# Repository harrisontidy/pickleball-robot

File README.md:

# Autonomous Pickleball Robot

An autonomous robot being developed to play pickleball against a human. It is designed to watch an incoming shot, move into position, and swing a paddle to return the ball across the net.

The goal is to create a practice partner that can react to your shots and keep a rally going.

## Playing a rally

The planned vision system uses a camera and YOLO object detection to locate the pickleball and follow its movement. From successive observations, the robot estimates where the ball is heading and where it needs to meet it.

The mobile base moves into position while the arm adjusts the paddle's angle. The swing mechanism is designed to time the stroke with the ball's arrival, return the shot, and bring the paddle back into position for the next ball.

The intended rally follows a continuous cycle:

1. Detect the incoming ball.
2. Track its path and estimate an interception point.
3. Move into position and line up the paddle.
4. Swing to return the shot.
5. Reset and watch for the next ball.

## Manual control

The robot also has a phone control page for driving, adjusting the paddle joints, and triggering swing sequences. These controls let the drive and paddle movements be tested individually while the autonomous rally system is developed.

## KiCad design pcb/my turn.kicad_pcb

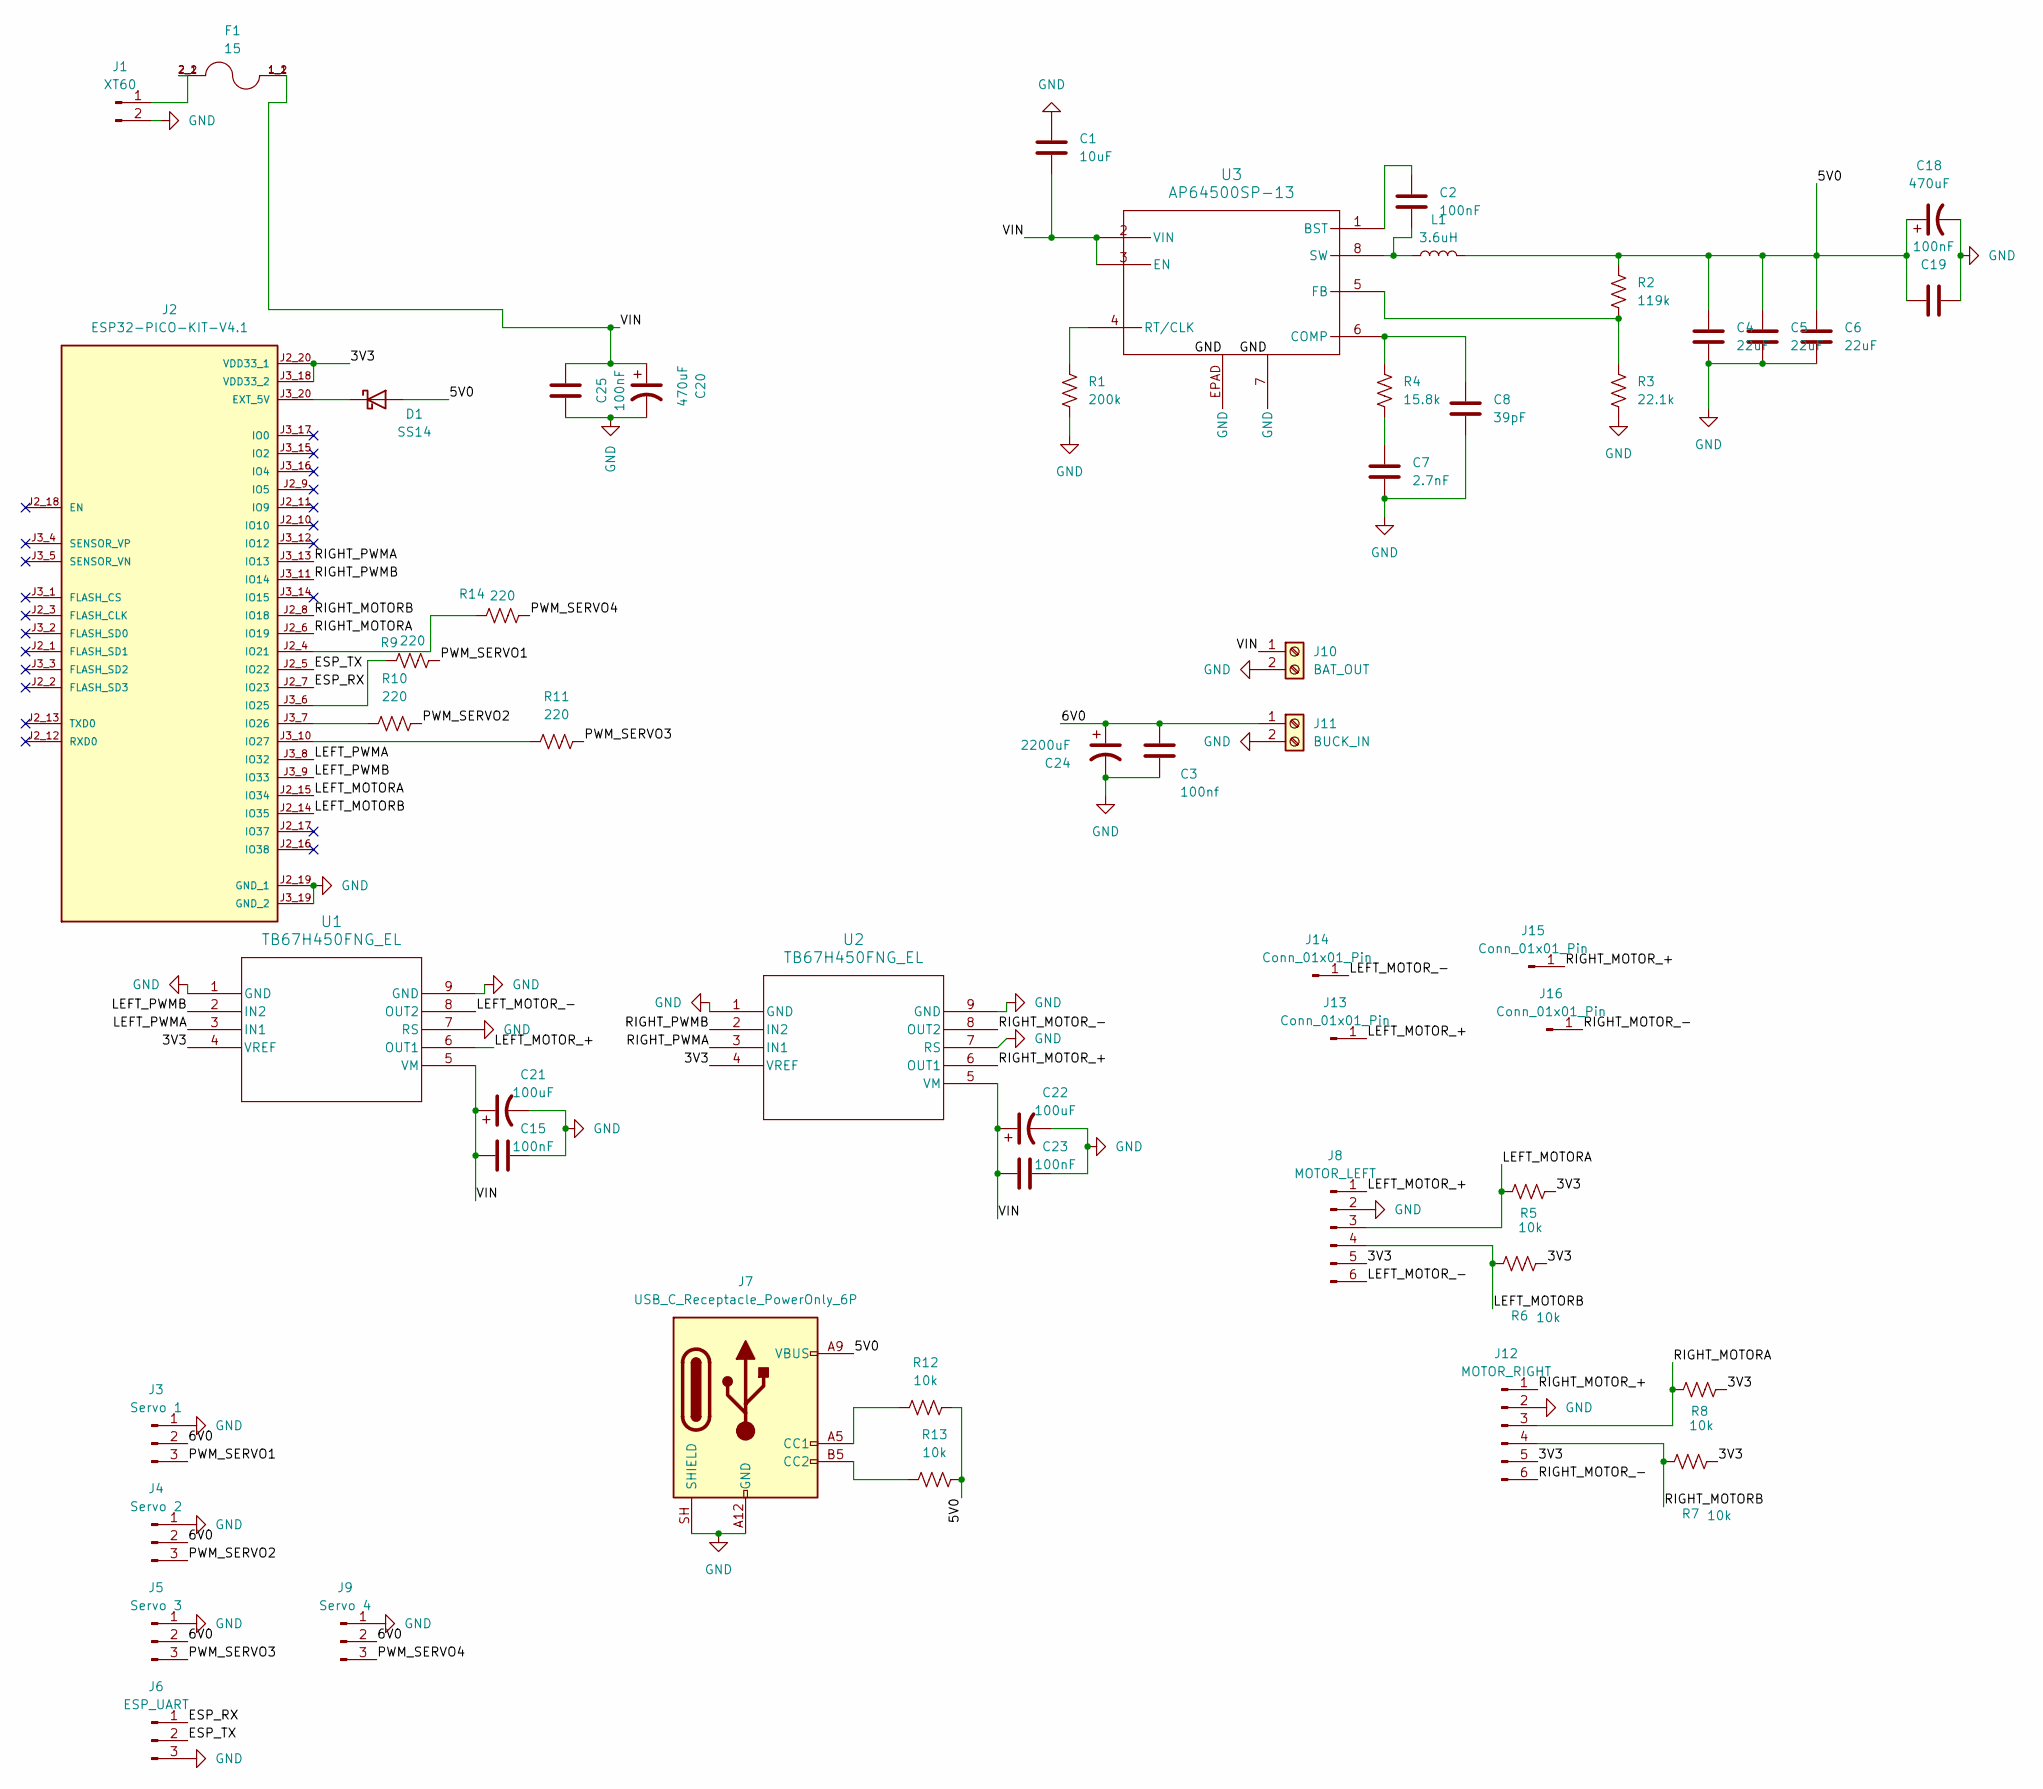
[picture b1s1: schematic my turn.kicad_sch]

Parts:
C1: 10uF; C_0805_2012Metric
C2, C15, C19, C23, C25: 100nF; C_0805_2012Metric
C3: 100nf; C_0805_2012Metric
C4, C5, C6: 22uF; C_0805_2012Metric
C7: 2.7nF; C_0805_2012Metric
C8: 39pF; C_0805_2012Metric
C18, C20: 470uF; CP_Radial_D10.0mm_P5.00mm
C21, C22: 100uF; CP_Radial_D8.0mm_P3.50mm
C24: 2200uF; CP_Radial_D12.5mm_P5.00mm
D1: SS14; D_SMA
F1: 15; FUSE_3587; PARTREV D
J1: XT60; AMASS_XT60-F_1x02_P7.20mm_Vertical
J2: ESP32-PICO-KIT-V4.1; XCVR_ESP32-PICO-KIT-V4.1; PARTREV 4.1
J3: Servo 1; PinHeader_1x03_P2.54mm_Vertical
J4: Servo 2; PinHeader_1x03_P2.54mm_Vertical
J5: Servo 3; PinHeader_1x03_P2.54mm_Vertical
J6: ESP_UART; PinHeader_1x03_P2.54mm_Vertical
J7: USB_C_Receptacle_PowerOnly_6P; USB_C_Receptacle_HRO_TYPE-C-31-M-17
J8: MOTOR_LEFT; JST_PH_B6B-PH-K_1x06_P2.00mm_Vertical
J9: Servo 4; PinHeader_1x03_P2.54mm_Vertical
J10: BAT_OUT; TerminalBlock_Phoenix_MKDS-1,5-2-5.08_1x02_P5.08mm_Horizont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
J11: BUCK_IN; TerminalBlock_Phoenix_MKDS-1,5-2-5.08_1x02_P5.08mm_Horizont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
J12: MOTOR_RIGHT; JST_PH_B6B-PH-K_1x06_P2.00mm_Vertical
J13, J14, J15, J16: Conn_01x01_Pin; Motor TH Pad
L1: 3.6uH; L_Sumida_CDRH127_L125
R1: 200k; R_0805_2012Metric
R2: 119k; R_0805_2012Metric
R3: 22.1k; R_0805_2012Metric
R4: 15.8k; R_0805_2012Metric
R5, R6, R7, R8, R12, R13: 10k; R_0805_2012Metric
R9, R10, R11, R14: 220; R_0805_2012Metric
U1, U2: TB67H450FNG_EL; P-HSOP8-0405-1p27-002_TOS
U3: AP64500SP-13; SO-8EP_DIO

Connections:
/3V3: J2.J2_20 (VDD33_1), J2.J3_18 (VDD33_2), J8.5, J12.5, R5.2, R6.2, R7.2, R8.2, U1.4 (VREF), U2.4 (VREF)
/5V0: C4.1, C5.2, C6.2, C18.1, C19.1, D1.2 (A), J7.A9 (VBUS), J7.B9 (VBUS), L1.2, R2.1, R12.2, R13.2
/6V0: C3.1, C24.1, J3.2, J4.2, J5.2, J9.2, J11.1
/ESP_RX: J2.J2_7 (IO23), J6.1
/ESP_TX: J2.J2_5 (IO22), J6.2
/LEFT_MOTORA: J2.J2_15 (IO34), J8.3, R5.1
/LEFT_MOTORB: J2.J2_14 (IO35), J8.4, R6.1
/LEFT_MOTOR_+: J8.1, J13.1 (Pin_1_1), U1.6 (OUT1)
/LEFT_MOTOR_-: J8.6, J14.1 (Pin_1_1), U1.8 (OUT2)
/LEFT_PWMA: J2.J3_8 (IO32), U1.3 (IN1)
/LEFT_PWMB: J2.J3_9 (IO33), U1.2 (IN2)
/PWM_SERVO1: J3.3, R9.2
/PWM_SERVO2: J4.3, R10.2
/PWM_SERVO3: J5.3, R11.2
/PWM_SERVO4: J9.3, R14.2
/RIGHT_MOTORA: J2.J2_6 (IO19), J12.3, R8.1
/RIGHT_MOTORB: J2.J2_8 (IO18), J12.4, R7.1
/RIGHT_MOTOR_+: J12.1, J15.1 (Pin_1_1), U2.6 (OUT1)
/RIGHT_MOTOR_-: J12.6, J16.1 (Pin_1_1), U2.8 (OUT2)
/RIGHT_PWMA: J2.J3_13 (IO13), U2.3 (IN1)
/RIGHT_PWMB: J2.J3_11 (IO14), U2.2 (IN2)
/VIN: C1.2, C15.2, C20.1, C21.1, C22.1, C23.2, C25.1, F1.1_1, F1.1_2, J10.1, U1.5 (VM), U2.5 (VM), U3.2 (VIN), U3.3 (EN)
GND: C1.1, C3.2, C4.2, C5.1, C6.1, C7.2, C8.2, C15.1, C18.2, C19.2, C20.2, C21.2, C22.2, C23.1, C24.2, C25.2, J1.2, J2.J2_19 (GND_1), J2.J3_19 (GND_2), J3.1, J4.1, J5.1, J6.3, J7.A12 (GND), J7.B12 (GND), J7.SH (SHIELD), J8.2, J9.1, J10.2, J11.2, J12.2, R1.2, R3.2, U1.1 (GND), U1.7 (RS), U1.9 (GND), U2.1 (GND), U2.7 (RS), U2.9 (GND), U3.7 (GND), U3.EPAD (GND)
unnamed: C7.1, R4.2
unnamed: D1.1 (K), J2.J3_20 (EXT_5V)
unnamed: F1.2_1, F1.2_2, J1.1
unnamed: J2.J2_4 (IO21), R14.1
unnamed: J2.J3_6 (IO25), R9.1
unnamed: J2.J3_7 (IO26), R10.1
unnamed: J2.J3_10 (IO27), R11.1
unnamed: J7.A5 (CC1), R12.1
unnamed: J7.B5 (CC2), R13.1
unnamed: C2.1, U3.1 (BST)
unnamed: C8.1, R4.1, U3.6 (COMP)
unnamed: R2.2, R3.1, U3.5 (FB)
unnamed: R1.1, U3.4 (RT/CLK)
unnamed: C2.2, L1.1, U3.8 (SW)

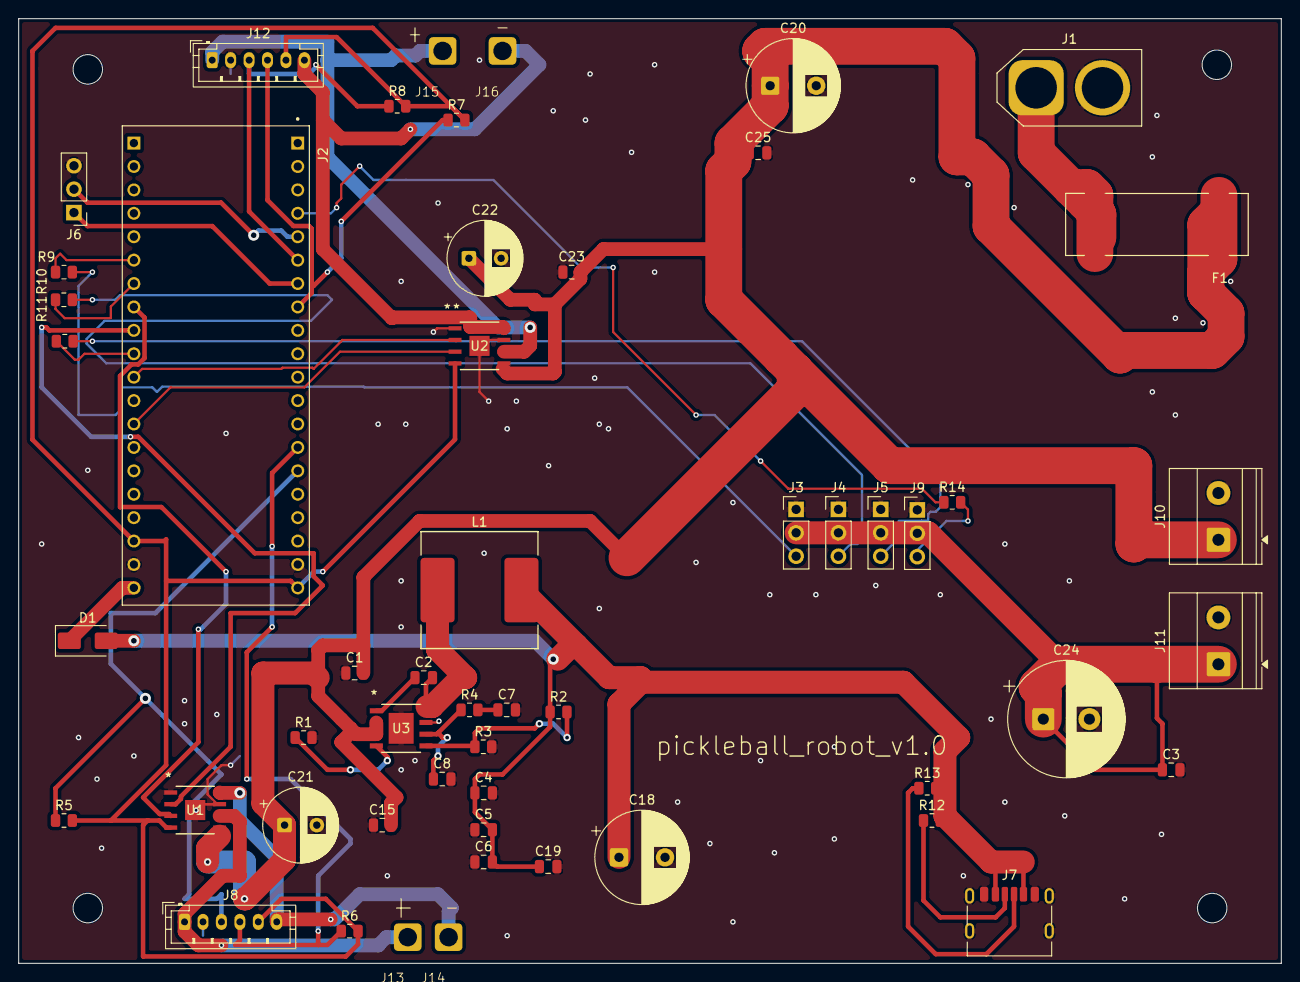
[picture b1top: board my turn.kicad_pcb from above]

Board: 2 copper layers, 137.0 x 102.5 mm, 53 parts (0 on the bottom side), 37 nets.
